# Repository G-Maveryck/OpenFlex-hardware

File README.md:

# OpenFlex-Project-hardware
Prototype for an Open source Flexfuel additionnal box

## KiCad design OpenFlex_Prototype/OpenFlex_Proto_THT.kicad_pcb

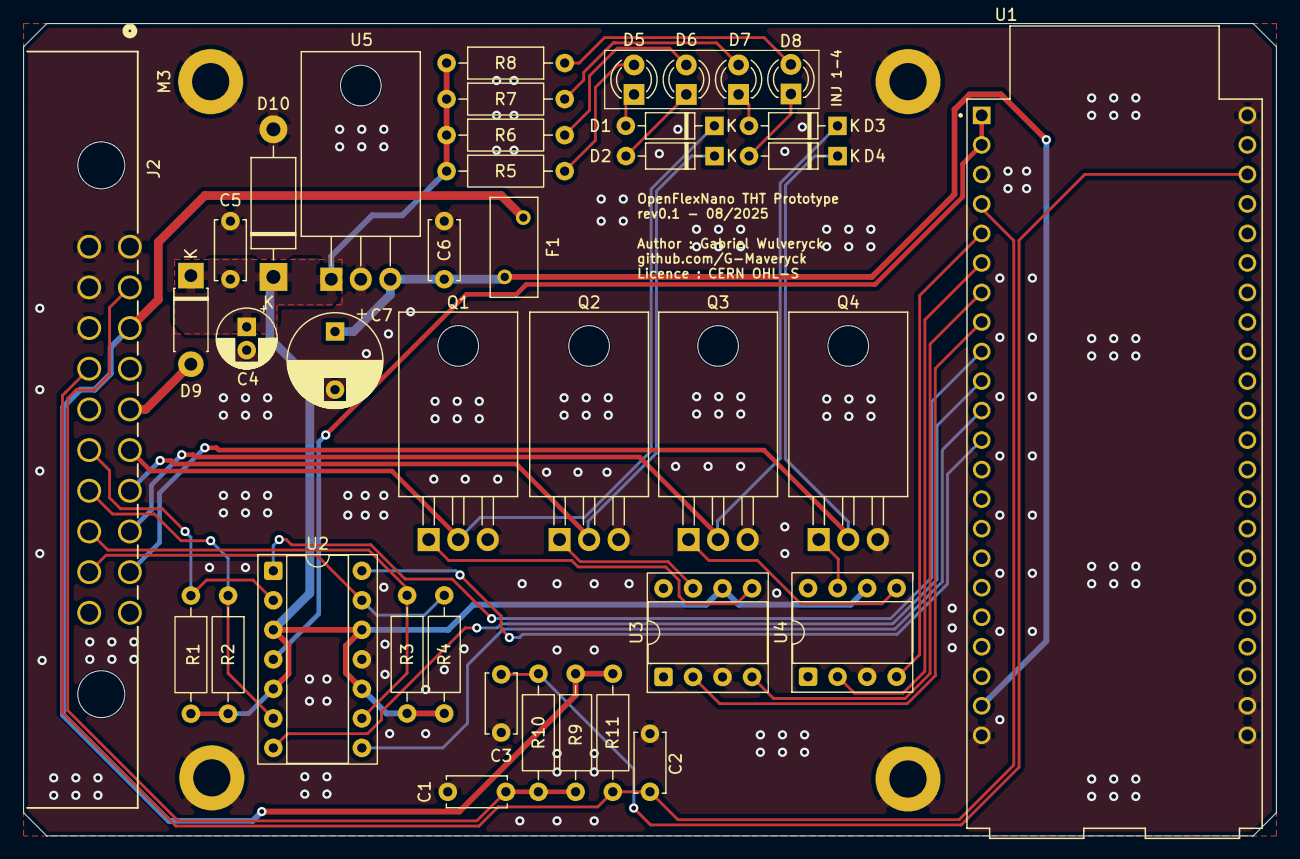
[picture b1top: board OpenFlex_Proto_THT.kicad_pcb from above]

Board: 2 copper layers, 107.8 x 69.9 mm, 43 parts (0 on the bottom side), 37 nets.

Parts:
C1: 100nF; C_Disc_D5.0mm_W2.5mm_P5.00mm
C2, C3: 220nF; C_Disc_D5.0mm_W2.5mm_P5.00mm
C4: 10uF; CP_Radial_D5.0mm_P2.00mm
C5, C6: 0.1uF; C_Disc_D5.0mm_W2.5mm_P5.00mm
C7: 47uF; CP_Radial_D8.0mm_P5.00mm
D1, D2, D3, D4: D; D_DO-35_SOD27_P7.62mm_Horizontal
D5, D6, D7, D8: LED; LED_D3.0mm
D9: SB230-E3/54; D_DO-41_SOD81_P7.62mm_Horizontal
D10: TP6KE47A; D_DO-15_P12.70mm_Horizontal
F1: Polyfuse; Fuse_BelFuse_0ZRE0005FF_L8.3mm_W3.8mm
J2: Molex MAX150_2x10; Molex_CONN_MX150_20w
M3, M3#2, M3#3, M3#4: MountingHole_3.2mm_M3_DIN965_Pad
Q1, Q2, Q3, Q4: STP80NF55-08; TO-220-3_Horizontal_TabDown
R1, R2, R3, R4: 10k; R_Axial_DIN0207_L6.3mm_D2.5mm_P10.16mm_Horizontal
R5, R6, R7, R8: 1k; R_Axial_DIN0207_L6.3mm_D2.5mm_P10.16mm_Horizontal
R9: 2.49k; R_Axial_DIN0207_L6.3mm_D2.5mm_P10.16mm_Horizontal
R10: 470R; R_Axial_DIN0207_L6.3mm_D2.5mm_P10.16mm_Horizontal
R11: 2.4k; R_Axial_DIN0207_L6.3mm_D2.5mm_P10.16mm_Horizontal
U1: ESP32-S2-DEVKITC-1; MODULE_ESP32-S2-DEVKITC-1
U2: LM324; DIP-14_W7.62mm_Socket
U3, U4: TC4424; DIP-8_W7.62mm_Socket
U5: LM2940S-5.0; TO-220-3_Horizontal_TabDown

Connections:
+12V: C4.1, C5.1, D9.1 (K), D10.1 (K), R1.2, R2.2, R3.2, R4.2, R5.1, R6.1, R7.1, R8.1, U2.3 (+), U2.5 (+), U2.10 (+), U2.12 (+), U3.6 (VDD), U4.6 (VDD), U5.1 (VI)
/Connector/Flex_snsr_SIGN: C2.1, J2.14, R11.2, U1.J1_4 (GPIO4)
/Connector/INJ_+12V: D9.2 (A), J2.5
/Connector/INJ_CH1: J2.16, R1.1, U2.2 (-)
/Connector/INJ_CH2: J2.17, R2.1, U2.6 (-)
/Connector/INJ_CH3: J2.18, R3.1, U2.9 (-)
/Connector/INJ_CH4: J2.19, R4.1, U2.13 (-)
/Connector/INJ_DRIVE_CH1: D1.1 (K), J2.6, Q1.2 (D)
/Connector/INJ_DRIVE_CH2: D2.1 (K), J2.7, Q2.2 (D)
/Connector/INJ_DRIVE_CH3: D3.1 (K), J2.8, Q3.2 (D)
/Connector/INJ_DRIVE_CH4: D4.1 (K), J2.9, Q4.2 (D)
/Connector/Temp_snsr_V+: C1.1, J2.2, R9.1, R10.2
/IO_Drivers/INJ_SIGNAL_CH1: U1.J1_9 (GPIO16), U2.1
/IO_Drivers/INJ_SIGNAL_CH2: U1.J1_10 (GPIO17), U2.7
/IO_Drivers/INJ_SIGNAL_CH3: U1.J1_11 (GPIO18), U2.8
/IO_Drivers/INJ_SIGNAL_CH4: U1.J1_12 (GPIO8), U2.14
/IO_Drivers/MCU_INJ1: U1.J1_7 (GPIO7), U3.4 (IN_B)
/IO_Drivers/MCU_INJ2: U1.J1_8 (GPIO15), U3.2 (IN_A)
/IO_Drivers/MCU_INJ3: U1.J1_5 (GPIO5), U4.4 (IN_B)
/IO_Drivers/MCU_INJ4: U1.J1_6 (GPIO6), U4.2 (IN_A)
/IO_Drivers/Temp_Signal: C3.1, R10.1, U1.J3_3 (U0RXD)
GND: C1.2, C2.2, C3.2, C4.2, C5.2, C6.2, C7.2, D10.2 (A), J2.1, J2.11, J2.12, J2.13, M3.1, M3#2.1, M3#3.1, M3#4.1, Q1.3 (S), Q2.3 (S), Q3.3 (S), Q4.3 (S), U1.J1_22 (GND_J1_22), U1.J3_1 (GND_J3_1), U1.J3_21 (GND_J3_21), U1.J3_22 (GND_J3_22), U2.11 (V-), U3.3 (GND), U4.3 (GND), U5.2 (GND)
unnamed: D1.2 (A), D5.1 (K)
unnamed: D2.2 (A), D6.1 (K)
unnamed: D3.2 (A), D7.1 (K)
unnamed: D4.2 (A), D8.1 (K)
unnamed: D5.2 (A), R5.2
unnamed: D6.2 (A), R6.2
unnamed: D7.2 (A), R7.2
unnamed: D8.2 (A), R8.2
unnamed: Q1.1 (G), U3.5 (OUT_B)
unnamed: Q2.1 (G), U3.7 (OUT_A)
unnamed: Q3.1 (G), U4.5 (OUT_B)
unnamed: Q4.1 (G), U4.7 (OUT_A)
VDD: C6.1, C7.1, F1.2, U1.J1_21 (VCC_5V), U5.3 (VO)
VDDA: F1.1, J2.3, R9.2, R11.1
VSS: U1.J1_1 (3V3_J1_1), U1.J1_2 (3V3_J1_2), U2.4 (V+)

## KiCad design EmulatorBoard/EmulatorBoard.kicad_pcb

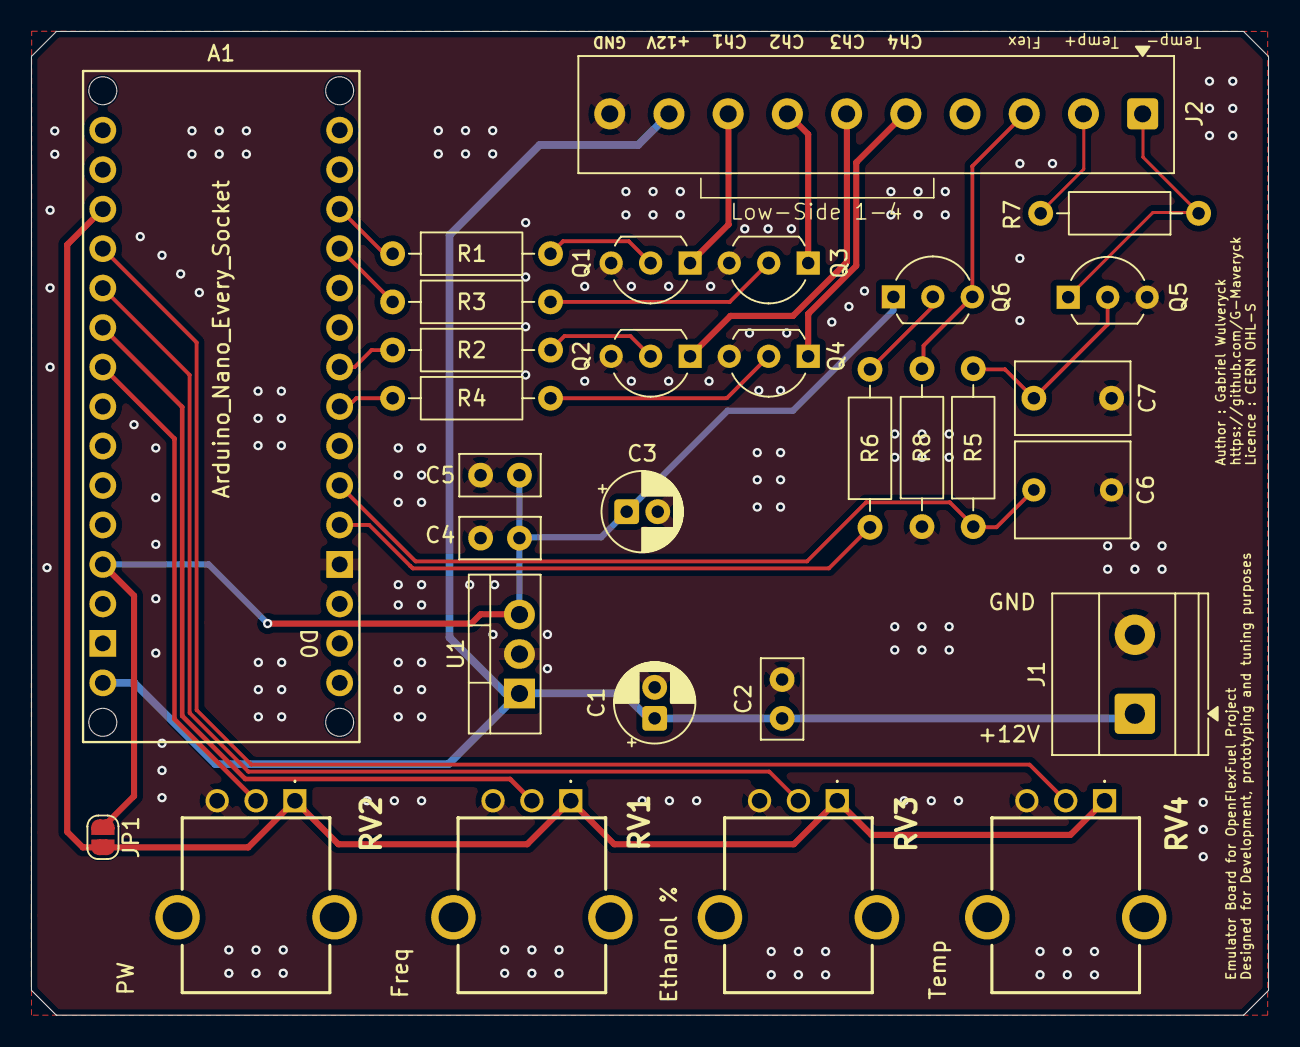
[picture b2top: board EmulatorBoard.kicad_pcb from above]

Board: 2 copper layers, 79.6 x 63.3 mm, 30 parts (0 on the bottom side), 27 nets.

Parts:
A1: Arduino_Nano_Every_Socket
C1, C3: 10uF; CP_Radial_D5.0mm_P2.00mm
C2, C4: 1nF; C_Disc_D5.0mm_W2.5mm_P2.50mm
C5: 100nF; C_Disc_D5.0mm_W2.5mm_P2.50mm
C6: 1uF; C_Rect_L7.2mm_W6.0mm_P5.00mm
C7: 100nF; C_Rect_L7.2mm_W4.5mm_P5.00mm_FKS2_FKP2_MKS2_MKP2
J1: Screw_Terminal_01x02; TerminalBlock_Phoenix_MKDS-1,5-2-5.08_1x02_P5.08mm_Horizont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
J2: Screw_Terminal_01x10; TerminalBlock_Phoenix_MKDS-1-10-3.81_1x10_P3.81mm_Horizontal
JP1: SolderJumper_2_Open; SolderJumper-2_P1.3mm_Open_RoundedPad1.0x1.5mm
Q1, Q2, Q3, Q4, Q5, Q6: 2N2222A; TO-92L_Inline_Wide
R1, R2, R3, R4, R5, R6, R7, R8: 1k; R_Axial_DIN0207_L6.3mm_D2.5mm_P10.16mm_Horizontal
RV1, RV2, RV3, RV4: 100k Lin; PTN091V100115K1B
U1: LM7805_TO220; TO-220-3_Vertical

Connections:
+12V: A1.VIN, C1.1, C2.1, J1.1, J2.9, U1.1 (VI)
/AREF_Pin: A1.AREF, JP1.2 (B), RV1.1, RV2.1, RV3.1, RV4.1
/Eperct_Pot: A1.A1, RV3.2
/FREQ_Pot: A1.A2, RV1.2
/GD_CH1: A1.D10, R1.1
/GD_CH2: A1.D9, R3.1
/GD_CH3: A1.D6, R2.1
/GD_CH4: A1.D5, R4.1
/INJ_CH1: J2.8, Q1.1 (C)
/INJ_CH2: J2.7, Q3.1 (C)
/INJ_CH3: J2.6, Q2.1 (C)
/INJ_CH4: J2.5, Q4.1 (C)
/MCU_D2: A1.D2, R6.1
/MCU_D3: A1.D3, C6.1, R5.1
/PW_Pot: A1.A3, RV2.2
/Temp_Pot: A1.A0, RV4.2
Flex_SNSR_Signal: J2.3, Q6.3 (E), R8.2
GND: A1.GND1 (GND), A1.GND2 (GND), C1.2, C2.2, C3.2, C4.2, C5.2, C6.2, C7.2, J1.2, J2.10, Q1.3 (E), Q2.3 (E), Q3.3 (E), Q4.3 (E), Q5.3 (E), R8.1, RV1.3, RV2.3, RV3.3, RV4.3, U1.2 (GND)
unnamed: Q1.2 (B), R1.2
unnamed: Q2.2 (B), R2.2
unnamed: Q3.2 (B), R3.2
unnamed: Q4.2 (B), R4.2
unnamed: C7.1, Q5.2 (B), R5.2
unnamed: Q6.2 (B), R6.2
Temp_+: J2.2, R7.2
Temp_-: J2.1, Q5.1 (C), R7.1
VDD: A1.5V, C3.1, C4.1, C5.1, JP1.1 (A), Q6.1 (C), U1.3 (VO)

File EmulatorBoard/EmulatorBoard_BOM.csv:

"Reference","Qty","Value","DNP","Exclude from BOM","Exclude from Board","Footprint","Datasheet"
"A1","1","Arduino_Nano_Every_Socket","","","","PCM_arduino-library:Arduino_Nano_Every_Socket","https://docs.arduino.cc/hardware/nano-every"
"C1,C3","2","10uF","","","","Capacitor_THT:CP_Radial_D5.0mm_P2.00mm",""
"C2,C4","2","1nF","","","","Capacitor_THT:C_Disc_D5.0mm_W2.5mm_P2.50mm",""
"C5","1","100nF","","","","Capacitor_THT:C_Disc_D5.0mm_W2.5mm_P2.50mm",""
"C6","1","1uF","","","","Capacitor_THT:C_Rect_L7.2mm_W6.0mm_P5.00mm",""
"C7","1","100nF","","","","Capacitor_THT:C_Rect_L7.2mm_W4.5mm_P5.00mm_FKS2_FKP2_MKS2_MKP2",""
"J1","1","Screw_Terminal_01x02","","","","TerminalBlock_Phoenix:TerminalBlock_Phoenix_MKDS-1,5-2-5.08_1x02_P5.08mm_Horizontal",""
"J2","1","Screw_Terminal_01x10","","","","TerminalBlock_Phoenix:TerminalBlock_Phoenix_MKDS-1-10-3.81_1x10_P3.81mm_Horizontal",""
"Q1,Q2,Q3,Q4,Q5,Q6","6","2N2222A","","","","Package_TO_SOT_THT:TO-92L_Inline_Wide",""
"R1,R2,R3,R4,R5,R6,R7,R8","8","1k","","","","Resistor_THT:R_Axial_DIN0207_L6.3mm_D2.5mm_P10.16mm_Horizontal",""
"RV1,RV2,RV3,RV4","4","100k Lin","","","","OpenFlex_FootPrint_Lib:PTN091V100115K1B",""
"U1","1","LM7805_TO220","","","","Package_TO_SOT_THT:TO-220-3_Vertical","https://www.onsemi.cn/PowerSolutions/document/MC7800-D.PDF"

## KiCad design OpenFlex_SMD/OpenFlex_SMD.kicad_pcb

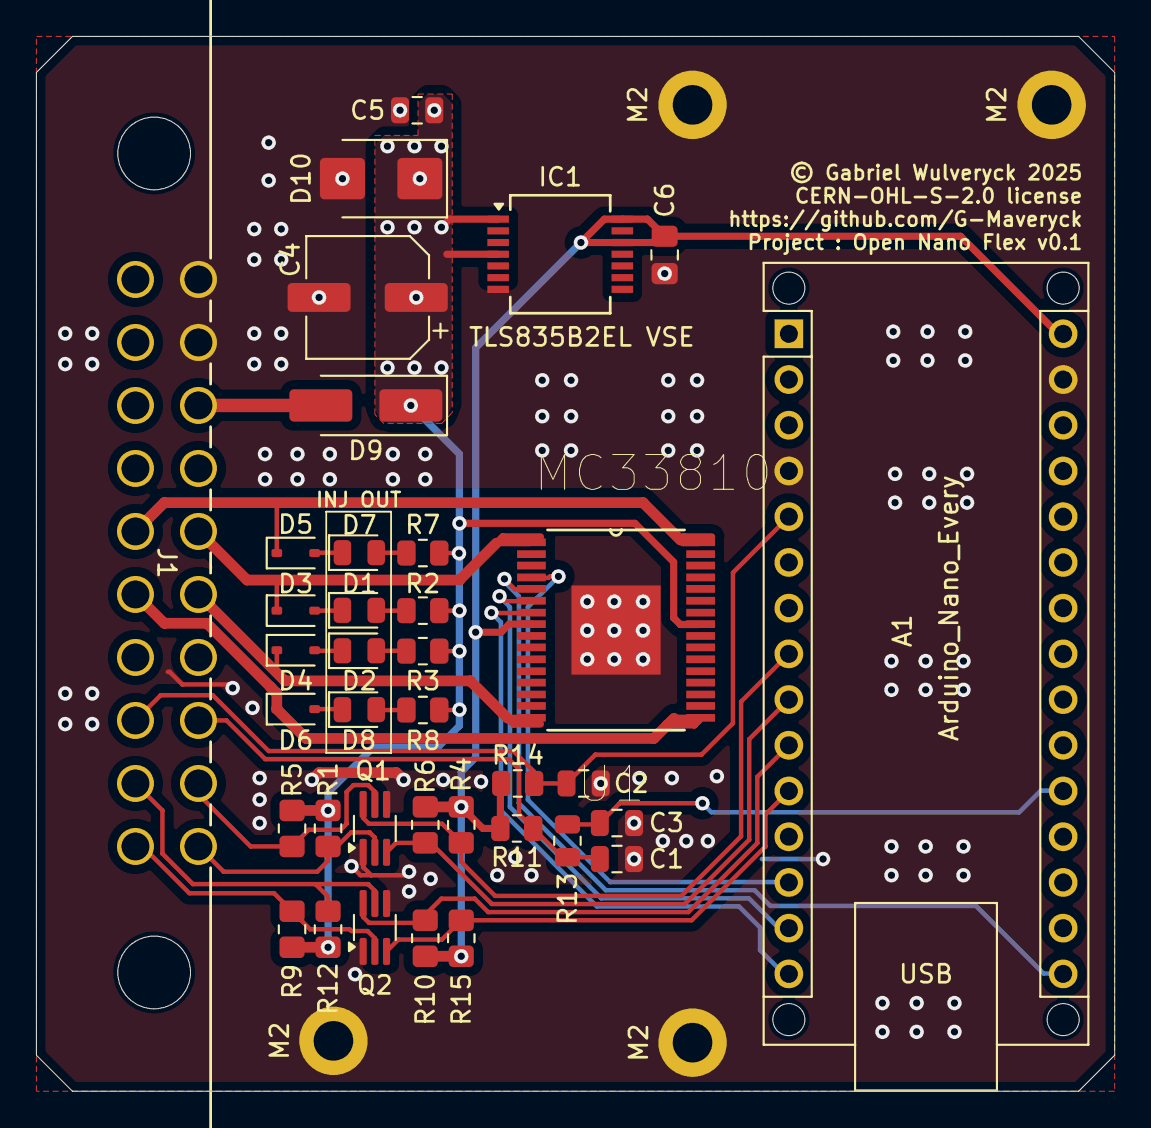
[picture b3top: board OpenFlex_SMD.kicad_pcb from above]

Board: 2 copper layers, 59.9 x 58.6 mm, 41 parts (0 on the bottom side), 31 nets.

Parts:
A1: Arduino_Nano_Every; Arduino_Nano_WithMountingHoles
C1: 0.1uF; C_0805_2012Metric
C2: 270nF; C_0805_2012Metric
C3: 0.22uF; C_0805_2012Metric
C4: 33uF; CP_Elec_6.3x7.7
C5: 100nF; C_0805_2012Metric
C6: 1uF; C_0805_2012Metric_Pad1.18x1.45mm_HandSolder
D1, D2, D7, D8: LED; LED_0805_2012Metric
D3, D4, D5, D6: D; D_SOD-323
D9: B360A-13-F; D_SMA_Handsoldering
D10: SMBJ40A-Q; D_SMB
IC1: TLS835B2EL VSE; SSOP-14_5.3x6.2mm_P0.65mm
J1: Conn_02x10_Counter_Clockwise; Molex_CONN_MX150_20w
M2, M2#2, M2#3, M2#4: MountingHole_2.2mm_M2_DIN965_Pad
Q1, Q2: Q_Dual_NMOS_S1G1D2S2G2D1; SOT-363_SC-70-6_Handsoldering
R1, R5, R9, R12: 10k; R_0805_2012Metric_Pad1.20x1.40mm_HandSolder
R2, R3, R7, R8: 1k; R_0805_2012Metric
R4, R6, R10, R15: 1k; R_0805_2012Metric_Pad1.20x1.40mm_HandSolder
R11: 2.49k; R_0805_2012Metric
R13: 470R; R_0805_2012Metric
R14: 2.4k; R_0805_2012Metric
U1: MC33810; SOIC32-P0.65-33N

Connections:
+5V: A1.30 (VIN), C6.1, IC1.12 (SEL), IC1.14 (OUT/Q), R4.1, R6.1, R10.1, R11.2, R14.1, R15.1, U1.8 (VDD)
+12V: C4.1, C5.1, D9.1 (K), D10.1 (K), IC1.1 (IN), IC1.4 (EN), R1.2, R2.1, R3.1, R5.2, R7.2, R8.2, R9.2, R12.2, U1.25 (VPWR)
/Connector/Flex_snsr: A1.5 (D2), C2.1, J1.18, R14.2
/Connector/INJ_+12V: D9.2 (A), J1.3
/Connector/INJ_CH1: J1.10, Q1.2 (G), R1.1
/Connector/INJ_CH2: J1.9, Q1.5 (G), R5.1
/Connector/INJ_CH3: J1.20, Q2.2 (G), R9.1
/Connector/INJ_CH4: J1.19, Q2.5 (G), R12.1
/Connector/INJ_DRIVE_CH1: D5.1 (K), J1.15, U1.32 (OUT2)
/Connector/INJ_DRIVE_CH2: D3.1 (K), J1.5, U1.1 (OUT0)
/Connector/INJ_DRIVE_CH3: D4.1 (K), J1.6, U1.16 (OUT1)
/Connector/INJ_DRIVE_CH4: D6.1 (K), J1.16, U1.17 (OUT3)
/Connector/Temp_snsr: C1.1, J1.8, R11.1, R13.2
/IO_Drivers/INJ_SIGNAL_CH1: A1.8 (D5), Q1.6 (D), R4.2
/IO_Drivers/INJ_SIGNAL_CH2: A1.9 (D6), Q1.3 (D), R6.2
/IO_Drivers/INJ_SIGNAL_CH3: A1.10 (D7), Q2.6 (D), R10.2
/IO_Drivers/INJ_SIGNAL_CH4: A1.11 (D8), Q2.3 (D), R15.2
/IO_Drivers/MC33810_CS: A1.13 (D10), U1.4 (CS)
/IO_Drivers/MISO: A1.15 (MISO), U1.7 (SO)
/IO_Drivers/MOSI: A1.14 (MOSI), U1.6 (SI)
/IO_Drivers/SCLK: A1.16 (SCK), U1.5 (SCLK)
/IO_Drivers/Temp_Signal: A1.20 (A1), C3.1, R13.1
GND: A1.4 (GND), A1.29 (GND), C1.2, C2.2, C3.2, C4.2, C5.2, C6.2, D10.2 (A), IC1.7 (GND), J1.1, J1.2, M2.1, M2#2.1, M2#3.1, M2#4.1, Q1.1 (S), Q1.4 (S), Q2.1 (S), Q2.4 (S), U1.33 (GND)
unnamed: D1.2 (A), R2.2
unnamed: D1.1 (K), D3.2 (A)
unnamed: D2.2 (A), R3.2
unnamed: D2.1 (K), D4.2 (A)
unnamed: D5.2 (A), D7.1 (K)
unnamed: D6.2 (A), D8.1 (K)
unnamed: D7.2 (A), R7.1
unnamed: D8.2 (A), R8.1

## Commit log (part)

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2026-04-27 Initial Commit
    Choosed ESP32 for development platform. Production version will integrate the ESP32 SoC, and SMD componants.
2026-04-27 removed old stl pcb file
    useless lol
2026-05-26 Updated PCB to ESP32-S2-Devkit-C1
2026-05-28 Updated and sourced EmulatoBoard (DevBoard)
2026-05-28 Updated Sourcing for prototype
2026-05-29 Enclosure WIP
2026-05-30 Actualized file name
2026-06-05 Updated BOM

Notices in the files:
EmulatorBoard/EmulatorBoard.kicad_pcb:
Licence : CERN OHL-S
OpenFlex_SMD/OpenFlex_SMD.kicad_pcb:
© Gabriel Wulveryck 2025
CERN-OHL-S-2.0 license
